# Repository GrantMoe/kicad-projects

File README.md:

# kicad-projects
A place to put KiCAD stuff I've been working on

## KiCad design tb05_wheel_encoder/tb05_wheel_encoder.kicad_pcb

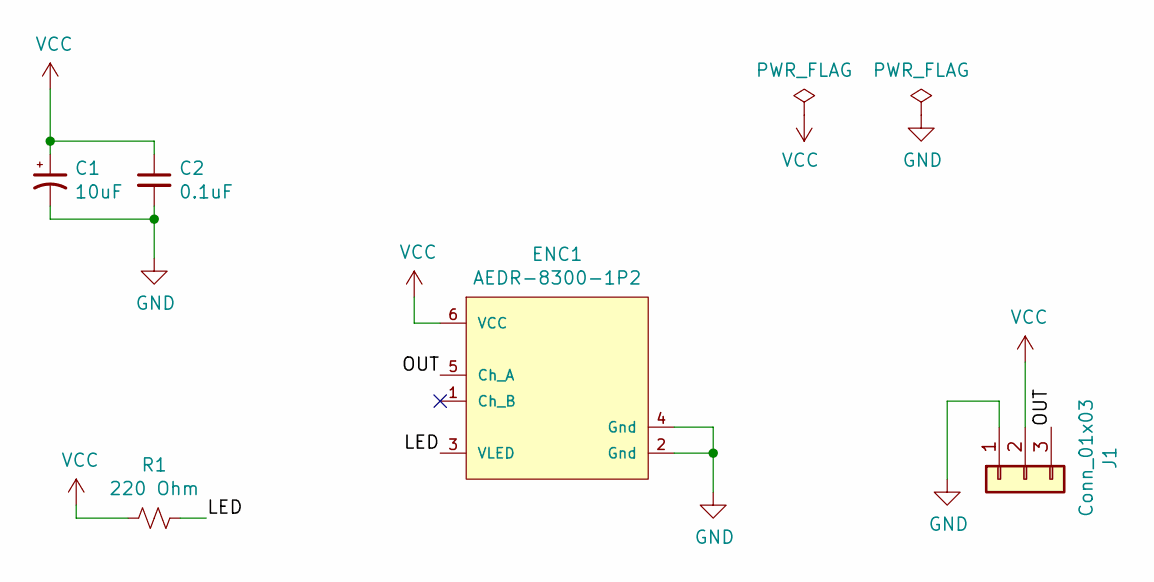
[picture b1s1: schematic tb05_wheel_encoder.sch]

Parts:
C1: 10uF; 0805
C2: 0.1uF; 0603
ENC1: AEDR-8300-1P2; Broadcom-AEDR-8300-1P2-0; mouser part number 630-AEDR-8300-1P2; digikey description ENCODER REFL OPT 2CH 150LPI 5V
J1: Conn_01x03; PinHeader_1x03_P2.54mm_Vertical
R1: 220 Ohm; 0603

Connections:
/LED: ENC1.3 (VLED), R1.1
/OUT: ENC1.5 (Ch_A), J1.3
GND: C1.2, C2.2, ENC1.2 (Gnd), ENC1.4 (Gnd), J1.1
VCC: C1.1, C2.1, ENC1.6 (VCC), J1.2, R1.2

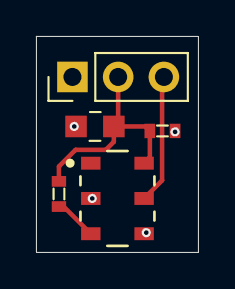
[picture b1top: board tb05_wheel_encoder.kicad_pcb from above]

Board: 2 copper layers, 9.0 x 12.0 mm, 5 parts (0 on the bottom side), 4 nets.

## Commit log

2021-02-14 Add wheel encoder project
2022-01-31 Add Jetson Nano control board
